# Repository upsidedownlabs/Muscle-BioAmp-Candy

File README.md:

# Muscle-BioAmp-Candy

[-white)](https://store.upsidedownlabs.tech/product/muscle-bioamp-candy/)

A candy size ElectroMyography (EMG) sensor for precise muscle bio-potential signals recording at an affordable cost. It comes with a fixed gain of x2420 and BandPass filter of 72Hz - 720Hz. To record the EMG signals you can use any standalone ADC like ADS1115 or any microcontroller development board with an ADC of your choice like Arduino UNO/Nano.

## Hardware

Muscle BioAmp Candy has been created using KiCad and all the design files can be found under [hardware](hardware/) folder. Images below shows a quick overview of the hardware design.

| PCB Front           |  PCB Back |
| :-------------------------: | :-------------------------: |
|   |  |

## License

| Licenses Facts              |  OSHWA Certification |
| :-------------------------: | :-------------------------: |
|   |  | 

#### Hardware
CERN Open Hardware License Version 2 - Strongly Reciprocal ([CERN-OHL-S-2.0](https://spdx.org/licenses/CERN-OHL-S-2.0.html)).

#### Software
MIT open source [license](http://opensource.org/licenses/MIT).

#### Documentation:
<br />This work is licensed under a <a rel="license" href="http://creativecommons.org/licenses/by/4.0/">Creative Commons Attribution 4.0 International License</a>.

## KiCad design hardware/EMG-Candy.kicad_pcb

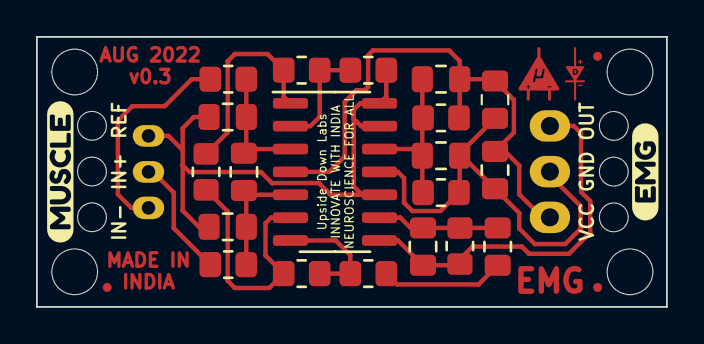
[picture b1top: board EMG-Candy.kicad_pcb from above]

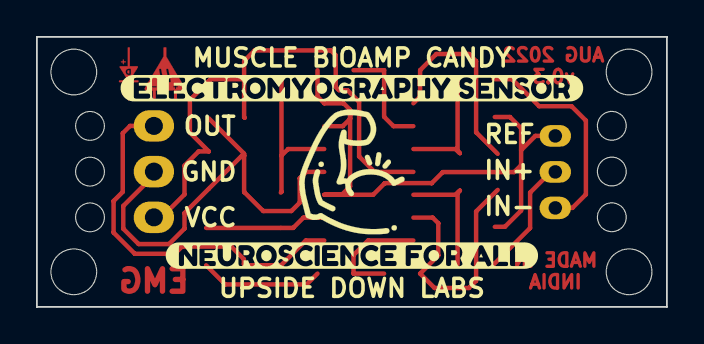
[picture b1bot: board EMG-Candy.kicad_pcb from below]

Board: 2 copper layers, 35.0 x 15.0 mm, 39 parts (4 on the bottom side), 13 nets.

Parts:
C1, C3: 100pF; C_0805_2012Metric_Pad1.18x1.45mm_HandSolder
C2, C7: 1nF; C_0805_2012Metric_Pad1.18x1.45mm_HandSolder
C4, C8: 100nF; C_0805_2012Metric_Pad1.18x1.45mm_HandSolder
C5, C6: 2.2uF; C_0805_2012Metric_Pad1.18x1.45mm_HandSolder
C9: 47uF; C_0805_2012Metric_Pad1.18x1.45mm_HandSolder
F1**, F2**, F3**: Fiducial_0.5mm_Mask1mm
H1, H2, H3, H4, H5, H6, H7, H8, H9, H10: MountingHole; MountingHole_2.1mm
J1: IO; PinHeader_1x03_P2.54mm_Horizontal
J3: BioAmp_input; JST_PH_S3B-PH-K_1x03_P2.00mm_Horizontal
R1, R2: 1K; R_0805_2012Metric_Pad1.20x1.40mm_HandSolder
R3, R4: 1M; R_0805_2012Metric_Pad1.20x1.40mm_HandSolder
R5: 1k; R_0805_2012Metric_Pad1.20x1.40mm_HandSolder
R6: 220K; R_0805_2012Metric_Pad1.20x1.40mm_HandSolder
R7, R10: 100k; R_0805_2012Metric_Pad1.20x1.40mm_HandSolder
R8, R9: 10k; R_0805_2012Metric_Pad1.20x1.40mm_HandSolder
U1: Amp; SOIC-14_3.9x8.7mm_P1.27mm
kibuzzard-62E8CB67: G***; kibuzzard-62E8CB67
kibuzzard-626BB171: G***; kibuzzard-626BB171
kibuzzard-626FA17E: G***; kibuzzard-626FA17E
kibuzzard-626FA157: G***; kibuzzard-626FA157

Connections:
+5V: C4.2, C8.2, C9.2, R3.2, U1.4 (V+)
GND: C5.1, C8.1, C9.1, R4.1, U1.11 (V-)
unnamed: C4.1, C5.2, R3.1, R4.2, U1.12 (+)
unnamed: C6.1, R5.1
unnamed: C6.2, C7.1, R6.2, U1.9 (-)
unnamed: R7.1, R8.2, U1.2 (-)
unnamed: R8.1, R9.2, U1.1
unnamed: R9.1, R10.2, U1.6 (-)
ampRef: C1.2, C3.1, R7.2, U1.10 (+), U1.13 (-), U1.14
bpfOUT: C7.2, R6.1, U1.8
inaIN+: C2.1, C3.2, R2.1, U1.5 (+)
inaIN-: C1.1, C2.2, R1.1, U1.3 (+)
inaOUT: R5.2, R10.1, U1.7

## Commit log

2022-12-12 Updare hardware files
2022-12-12 Update graphics
2022-12-12 Update gitignore
2022-12-12 Add interactive BOM
2022-12-12 Add Envelope code
2024-07-02 Upload svg file
    Add svg file of OSHW Certification of Muscle Bioamp Candy
2024-07-02 png of OSHW certification
2024-07-02 Updated the OSHW certification according to Bioamp Candy
2024-07-03 Create LICENSE.md
    Created a License file

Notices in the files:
README.md:
Open Source Licenses Facts  | Open Source Hardware Certification mark
